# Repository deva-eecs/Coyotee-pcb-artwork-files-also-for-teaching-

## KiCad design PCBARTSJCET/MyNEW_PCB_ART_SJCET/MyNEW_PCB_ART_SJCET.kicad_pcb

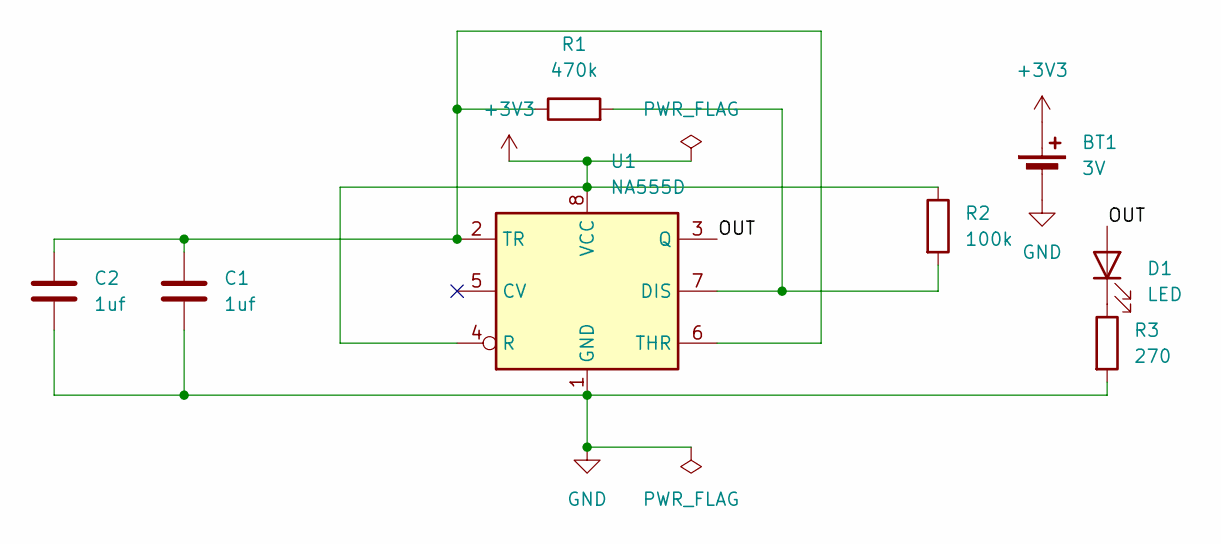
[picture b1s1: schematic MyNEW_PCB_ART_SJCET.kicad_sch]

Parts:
BT1: 3V; battery_pads
C1, C2: 1uf; C_1206_3216Metric
D1: LED; LED_0805_2012Metric
R1: 470k; R_1206_3216Metric
R2: 100k; R_0805_2012Metric
R3: 270; R_1206_3216Metric
U1: NA555D; SOIC-8_3.9x4.9mm_P1.27mm

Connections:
+3V3: BT1.1 (+), R2.1, U1.4 (R), U1.8 (VCC)
/OUT: D1.2 (A), U1.3 (Q)
GND: BT1.2 (-), C1.2, C2.2, R3.2, U1.1 (GND)
unnamed: D1.1 (K), R3.1
unnamed: R1.2, R2.2, U1.7 (DIS)
unnamed: C1.1, C2.1, R1.1, U1.2 (TR), U1.6 (THR)

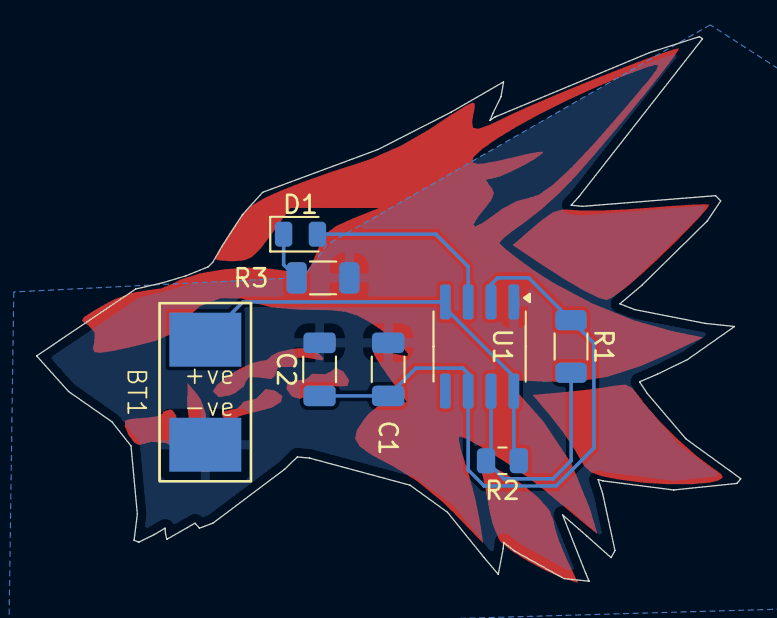
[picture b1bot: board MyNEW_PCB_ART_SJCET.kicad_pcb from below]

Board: 2 copper layers, 39.1 x 30.3 mm, 8 parts (8 on the bottom side), 6 nets.

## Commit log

2025-05-20 PCB COYOTEE FOLDER WITH Teaching docs
